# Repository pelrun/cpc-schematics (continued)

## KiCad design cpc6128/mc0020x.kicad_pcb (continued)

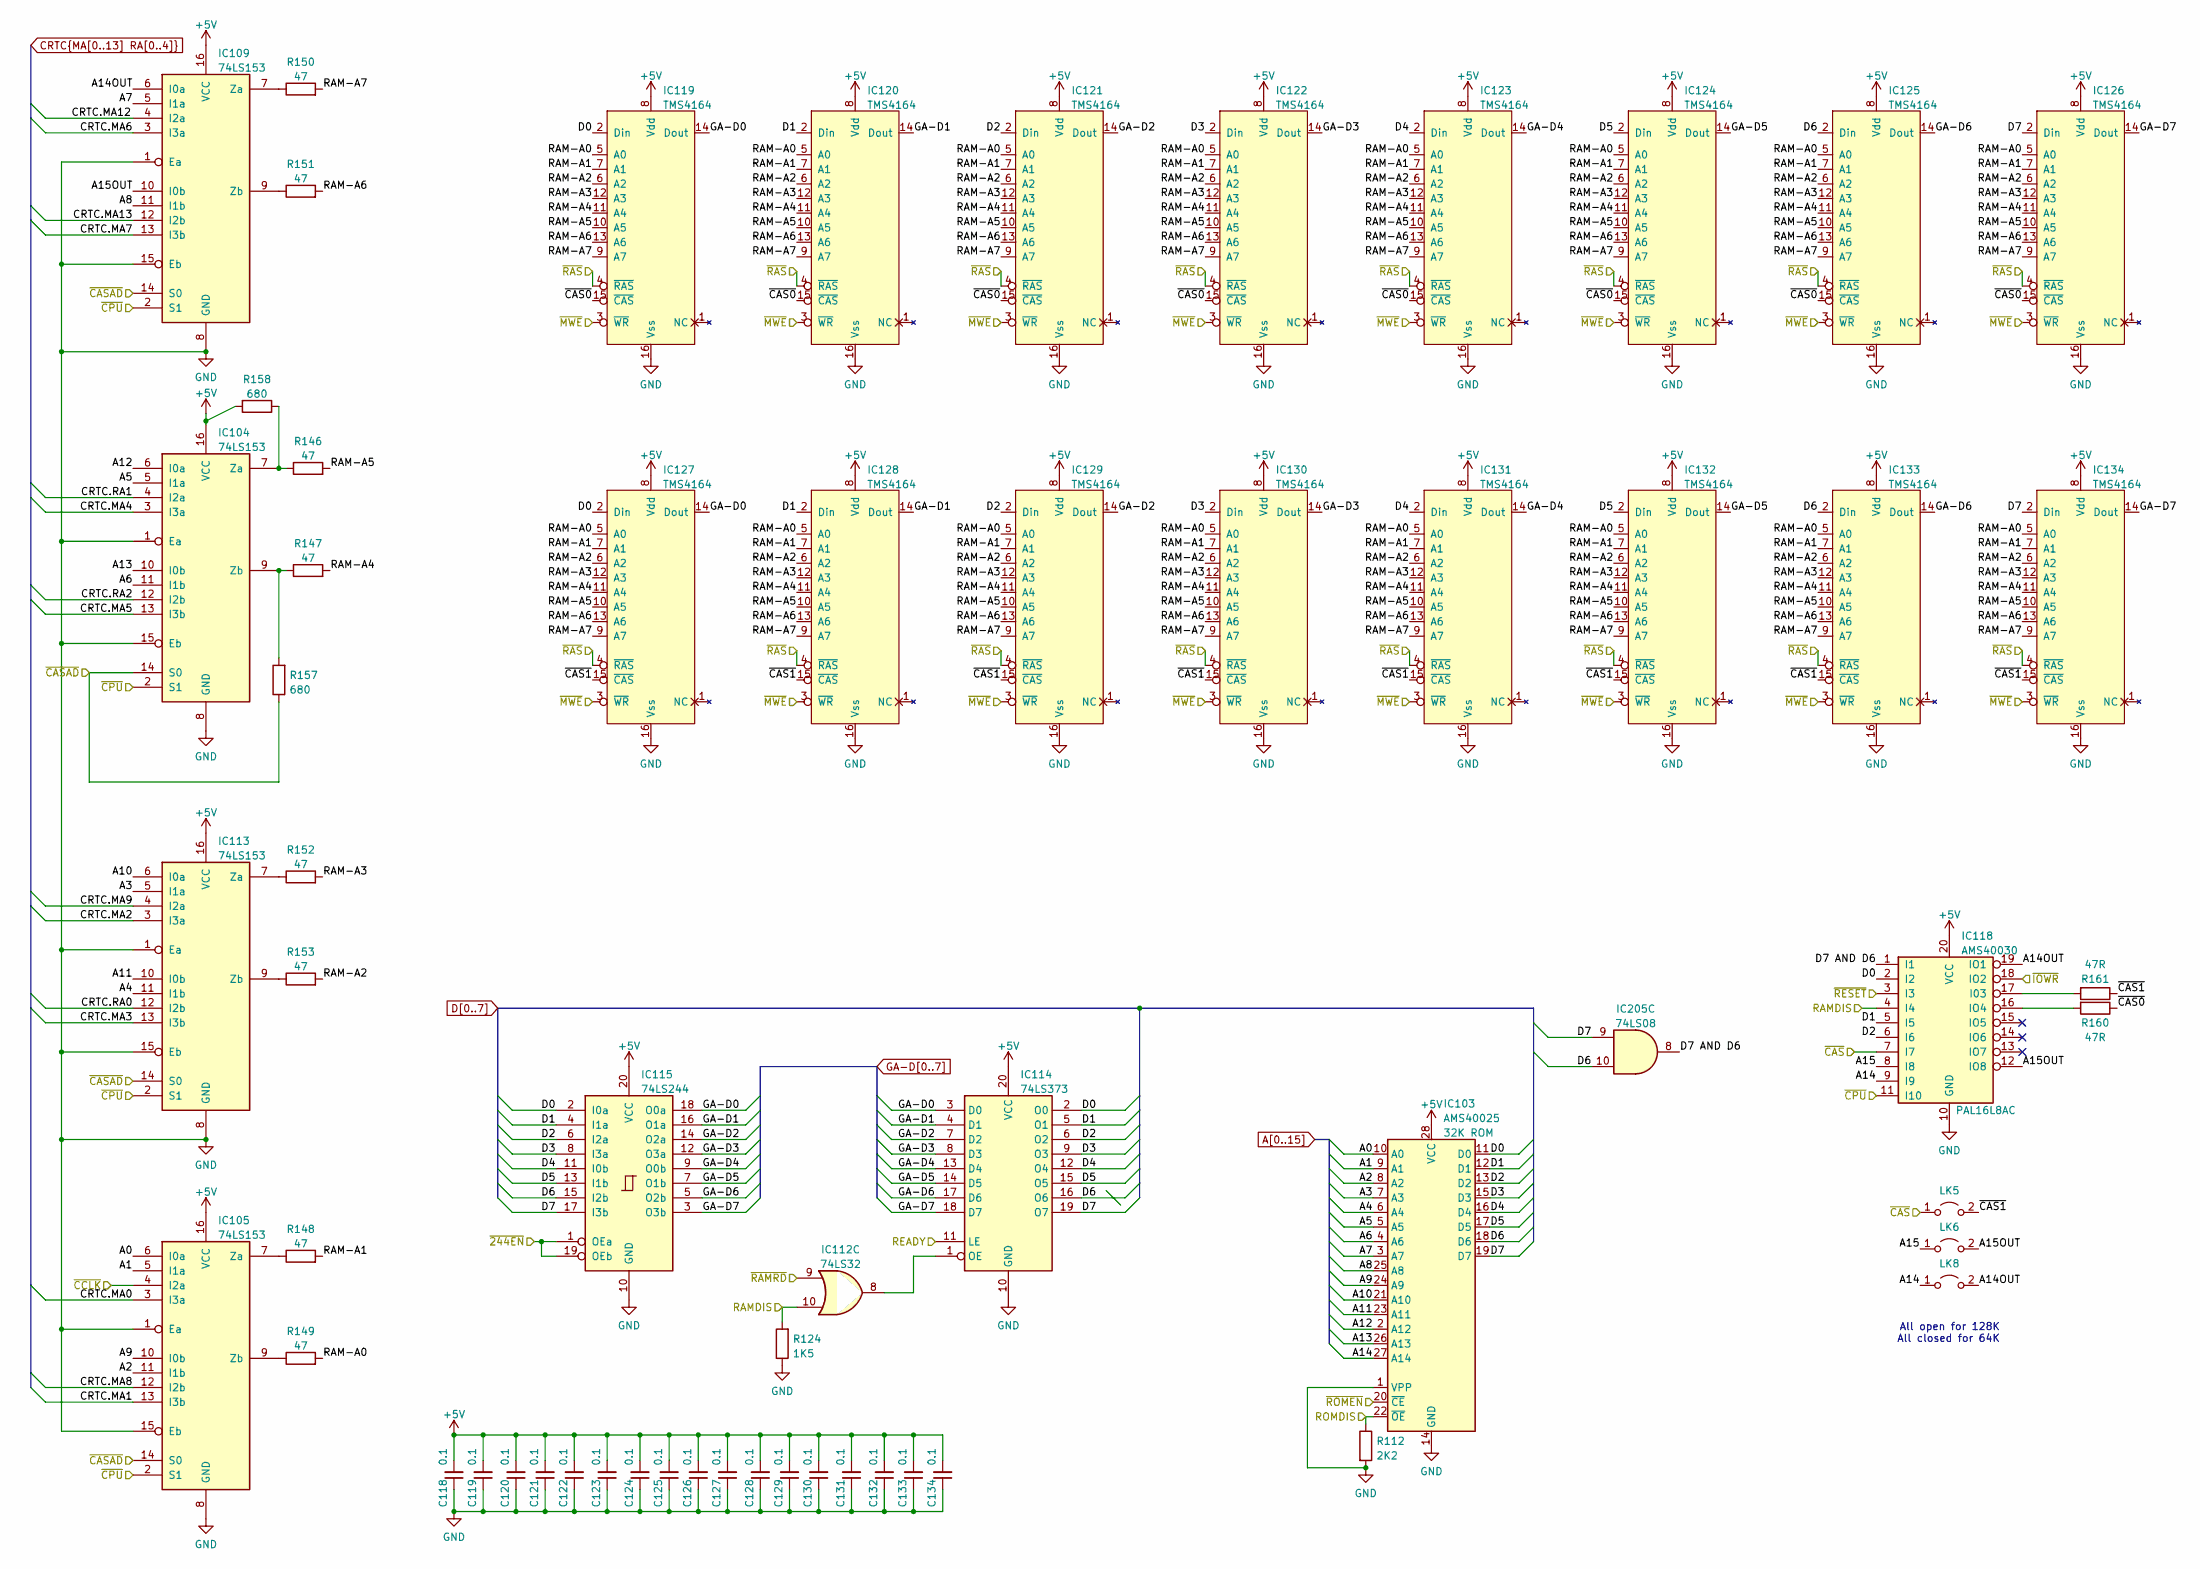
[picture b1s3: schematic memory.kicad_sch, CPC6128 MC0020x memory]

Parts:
C118, C119, C120, C121, C122, C123, C124, C125, C126, C127, C128, C129, C130, C131, C132, C133, C134: 0.1; C_Disc_D4.3mm_W1.9mm_P5.00mm
IC103: AMS40025; DIP-28_W15.24mm
IC104, IC105, IC109, IC113: 74LS153; DIP-16_W7.62mm
IC112: 74LS32; DIP-14_W7.62mm
IC114: 74LS373; DIP-20_W7.62mm
IC115: 74LS244; DIP-20_W7.62mm
IC118: AMS40030; DIP-20_W7.62mm_Socket
IC119, IC120, IC121, IC122, IC123, IC124, IC125, IC126, IC127, IC128, IC129, IC130, IC131, IC132, IC133, IC134: TMS4164; DIP-16_W7.62mm
IC205: 74LS08; DIP-14_W7.62mm
LK5, LK6, LK8: Jumper_2_Open; LINK
R112: 2K2; R_Axial_DIN0207_L6.3mm_D2.5mm_P10.16mm_Horizontal
R124: 1K5; R_Axial_DIN0207_L6.3mm_D2.5mm_P10.16mm_Horizontal
R146, R147, R148, R149, R150, R151, R152, R153: 47; R_Axial_DIN0207_L6.3mm_D2.5mm_P10.16mm_Horizontal
R157, R158: 680; R_Axial_DIN0207_L6.3mm_D2.5mm_P10.16mm_Horizontal
R160, R161: 47R; R_Axial_DIN0207_L6.3mm_D2.5mm_P10.16mm_Horizontal

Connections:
+5V: C118.2, C119.2, C120.2, C121.2, C122.2, C123.2, C124.2, C125.2, C126.2, C127.2, C128.2, C129.2, C130.2, C131.2, C132.2, C133.2, C134.2, IC103.28 (VCC), IC104.16 (VCC), IC105.16 (VCC), IC109.16 (VCC), IC113.16 (VCC), IC114.20 (VCC), IC115.20 (VCC), IC118.20 (VCC), IC119.8 (Vdd), IC120.8 (Vdd), IC121.8 (Vdd), IC122.8 (Vdd), IC123.8 (Vdd), IC124.8 (Vdd), IC125.8 (Vdd), IC126.8 (Vdd), IC127.8 (Vdd), IC128.8 (Vdd), IC129.8 (Vdd), IC130.8 (Vdd), IC131.8 (Vdd), IC132.8 (Vdd), IC133.8 (Vdd), IC134.8 (Vdd), R158.2; also elsewhere on the board
/Memory/A14OUT: IC109.6 (I0a), IC118.19 (IO1), LK8.2 (B)
/Memory/A15OUT: IC109.10 (I0b), IC118.12 (IO8), LK6.2 (B)
/Memory/D7 AND D6: IC118.1 (I1), IC205.8
/Memory/RAM-A0: IC119.5 (A0), IC120.5 (A0), IC121.5 (A0), IC122.5 (A0), IC123.5 (A0), IC124.5 (A0), IC125.5 (A0), IC126.5 (A0), IC127.5 (A0), IC128.5 (A0), IC129.5 (A0), IC130.5 (A0), IC131.5 (A0), IC132.5 (A0), IC133.5 (A0), IC134.5 (A0), R149.2
/Memory/RAM-A1: IC119.7 (A1), IC120.7 (A1), IC121.7 (A1), IC122.7 (A1), IC123.7 (A1), IC124.7 (A1), IC125.7 (A1), IC126.7 (A1), IC127.7 (A1), IC128.7 (A1), IC129.7 (A1), IC130.7 (A1), IC131.7 (A1), IC132.7 (A1), IC133.7 (A1), IC134.7 (A1), R148.2
/Memory/RAM-A2: IC119.6 (A2), IC120.6 (A2), IC121.6 (A2), IC122.6 (A2), IC123.6 (A2), IC124.6 (A2), IC125.6 (A2), IC126.6 (A2), IC127.6 (A2), IC128.6 (A2), IC129.6 (A2), IC130.6 (A2), IC131.6 (A2), IC132.6 (A2), IC133.6 (A2), IC134.6 (A2), R153.2
/Memory/RAM-A3: IC119.12 (A3), IC120.12 (A3), IC121.12 (A3), IC122.12 (A3), IC123.12 (A3), IC124.12 (A3), IC125.12 (A3), IC126.12 (A3), IC127.12 (A3), IC128.12 (A3), IC129.12 (A3), IC130.12 (A3), IC131.12 (A3), IC132.12 (A3), IC133.12 (A3), IC134.12 (A3), R152.2
/Memory/RAM-A4: IC119.11 (A4), IC120.11 (A4), IC121.11 (A4), IC122.11 (A4), IC123.11 (A4), IC124.11 (A4), IC125.11 (A4), IC126.11 (A4), IC127.11 (A4), IC128.11 (A4), IC129.11 (A4), IC130.11 (A4), IC131.11 (A4), IC132.11 (A4), IC133.11 (A4), IC134.11 (A4), R147.2
/Memory/RAM-A5: IC119.10 (A5), IC120.10 (A5), IC121.10 (A5), IC122.10 (A5), IC123.10 (A5), IC124.10 (A5), IC125.10 (A5), IC126.10 (A5), IC127.10 (A5), IC128.10 (A5), IC129.10 (A5), IC130.10 (A5), IC131.10 (A5), IC132.10 (A5), IC133.10 (A5), IC134.10 (A5), R146.2
/Memory/RAM-A6: IC119.13 (A6), IC120.13 (A6), IC121.13 (A6), IC122.13 (A6), IC123.13 (A6), IC124.13 (A6), IC125.13 (A6), IC126.13 (A6), IC127.13 (A6), IC128.13 (A6), IC129.13 (A6), IC130.13 (A6), IC131.13 (A6), IC132.13 (A6), IC133.13 (A6), IC134.13 (A6), R151.2
/Memory/RAM-A7: IC119.9 (A7), IC120.9 (A7), IC121.9 (A7), IC122.9 (A7), IC123.9 (A7), IC124.9 (A7), IC125.9 (A7), IC126.9 (A7), IC127.9 (A7), IC128.9 (A7), IC129.9 (A7), IC130.9 (A7), IC131.9 (A7), IC132.9 (A7), IC133.9 (A7), IC134.9 (A7), R150.2
/Memory/~244EN: IC115.1 (OEa), IC115.19 (OEb); also elsewhere on the board
/Memory/~CAS0: IC119.15 (~CAS), IC120.15 (~CAS), IC121.15 (~CAS), IC122.15 (~CAS), IC123.15 (~CAS), IC124.15 (~CAS), IC125.15 (~CAS), IC126.15 (~CAS), R160.1
/Memory/~CAS1: IC127.15 (~CAS), IC128.15 (~CAS), IC129.15 (~CAS), IC130.15 (~CAS), IC131.15 (~CAS), IC132.15 (~CAS), IC133.15 (~CAS), IC134.15 (~CAS), LK5.2 (B), R161.1
/Memory/~CASAD: IC104.14 (S0), IC105.14 (S0), IC109.14 (S0), IC113.14 (S0), R157.1; also elsewhere on the board
/Memory/~CAS: IC118.7 (I7), LK5.1 (A); also elsewhere on the board
/Memory/~MWE: IC119.3 (~WR), IC120.3 (~WR), IC121.3 (~WR), IC122.3 (~WR), IC123.3 (~WR), IC124.3 (~WR), IC125.3 (~WR), IC126.3 (~WR), IC127.3 (~WR), IC128.3 (~WR), IC129.3 (~WR), IC130.3 (~WR), IC131.3 (~WR), IC132.3 (~WR), IC133.3 (~WR), IC134.3 (~WR); also elsewhere on the board
/Memory/~RAS: IC119.4 (~RAS), IC120.4 (~RAS), IC121.4 (~RAS), IC122.4 (~RAS), IC123.4 (~RAS), IC124.4 (~RAS), IC125.4 (~RAS), IC126.4 (~RAS), IC127.4 (~RAS), IC128.4 (~RAS), IC129.4 (~RAS), IC130.4 (~RAS), IC131.4 (~RAS), IC132.4 (~RAS), IC133.4 (~RAS), IC134.4 (~RAS); also elsewhere on the board
/RAMDIS: IC112.10, IC118.4 (I4), R124.2; also elsewhere on the board
/READY: IC114.11 (LE); also elsewhere on the board
/ROMDIS: IC103.22 (~OE), R112.1; also elsewhere on the board
/~CCLK: IC105.4 (I2a); also elsewhere on the board
/~CPU: IC104.2 (S1), IC105.2 (S1), IC109.2 (S1), IC113.2 (S1), IC118.11 (I10); also elsewhere on the board
/~IOWR: IC118.18 (IO2); also elsewhere on the board
/~RAMRD: IC112.9; also elsewhere on the board
/~RESET: IC118.3 (I3); also elsewhere on the board
/~ROMEN: IC103.20 (~CE); also elsewhere on the board
A0: IC103.10 (A0), IC105.6 (I0a); also elsewhere on the board
A1: IC103.9 (A1), IC105.5 (I1a); also elsewhere on the board
A2: IC103.8 (A2), IC105.11 (I1b); also elsewhere on the board
A3: IC103.7 (A3), IC113.5 (I1a); also elsewhere on the board
A4: IC103.6 (A4), IC113.11 (I1b); also elsewhere on the board
A5: IC103.5 (A5), IC104.5 (I1a); also elsewhere on the board
A6: IC103.4 (A6), IC104.11 (I1b); also elsewhere on the board
A7: IC103.3 (A7), IC109.5 (I1a); also elsewhere on the board
A8: IC103.25 (A8), IC109.11 (I1b); also elsewhere on the board
A9: IC103.24 (A9), IC105.10 (I0b); also elsewhere on the board
A10: IC103.21 (A10), IC113.6 (I0a); also elsewhere on the board
A11: IC103.23 (A11), IC113.10 (I0b); also elsewhere on the board
A12: IC103.2 (A12), IC104.6 (I0a); also elsewhere on the board
A13: IC103.26 (A13), IC104.10 (I0b); also elsewhere on the board
A14: IC103.27 (A14), IC118.9 (I9), LK8.1 (A); also elsewhere on the board
A15: IC118.8 (I8), LK6.1 (A); also elsewhere on the board
CRTC.MA0: IC105.3 (I3a); also elsewhere on the board
CRTC.MA1: IC105.13 (I3b); also elsewhere on the board
CRTC.MA2: IC113.3 (I3a); also elsewhere on the board
CRTC.MA3: IC113.13 (I3b); also elsewhere on the board
CRTC.MA4: IC104.3 (I3a); also elsewhere on the board
CRTC.MA5: IC104.13 (I3b); also elsewhere on the board
CRTC.MA6: IC109.3 (I3a); also elsewhere on the board
CRTC.MA7: IC109.13 (I3b); also elsewhere on the board
CRTC.MA8: IC105.12 (I2b); also elsewhere on the board
CRTC.MA9: IC113.4 (I2a); also elsewhere on the board
CRTC.MA12: IC109.4 (I2a); also elsewhere on the board
CRTC.MA13: IC109.12 (I2b); also elsewhere on the board
CRTC.RA0: IC113.12 (I2b); also elsewhere on the board
CRTC.RA1: IC104.4 (I2a); also elsewhere on the board
CRTC.RA2: IC104.12 (I2b); also elsewhere on the board
D0: IC103.11 (D0), IC114.2 (O0), IC115.2 (I0a), IC118.2 (I2), IC119.2 (Din), IC127.2 (Din); also elsewhere on the board
D1: IC103.12 (D1), IC114.5 (O1), IC115.4 (I1a), IC118.5 (I5), IC120.2 (Din), IC128.2 (Din); also elsewhere on the board
D2: IC103.13 (D2), IC114.6 (O2), IC115.6 (I2a), IC118.6 (I6), IC121.2 (Din), IC129.2 (Din); also elsewhere on the board
D3: IC103.15 (D3), IC114.9 (O3), IC115.8 (I3a), IC122.2 (Din), IC130.2 (Din); also elsewhere on the board
D4: IC103.16 (D4), IC114.12 (O4), IC115.11 (I0b), IC123.2 (Din), IC131.2 (Din); also elsewhere on the board
D5: IC103.17 (D5), IC114.15 (O5), IC115.13 (I1b), IC124.2 (Din), IC132.2 (Din); also elsewhere on the board
D6: IC103.18 (D6), IC114.16 (O6), IC115.15 (I2b), IC125.2 (Din), IC133.2 (Din), IC205.10; also elsewhere on the board
D7: IC103.19 (D7), IC114.19 (O7), IC115.17 (I3b), IC126.2 (Din), IC134.2 (Din), IC205.9; also elsewhere on the board
GA-D0: IC114.3 (D0), IC115.18 (O0a), IC119.14 (Dout), IC127.14 (Dout); also elsewhere on the board
GA-D1: IC114.4 (D1), IC115.16 (O1a), IC120.14 (Dout), IC128.14 (Dout); also elsewhere on the board
GA-D2: IC114.7 (D2), IC115.14 (O2a), IC121.14 (Dout), IC129.14 (Dout); also elsewhere on the board
GA-D3: IC114.8 (D3), IC115.12 (O3a), IC122.14 (Dout), IC130.14 (Dout); also elsewhere on the board
GA-D4: IC114.13 (D4), IC115.9 (O0b), IC123.14 (Dout), IC131.14 (Dout); also elsewhere on the board
GA-D5: IC114.14 (D5), IC115.7 (O1b), IC124.14 (Dout), IC132.14 (Dout); also elsewhere on the board
GA-D6: IC114.17 (D6), IC115.5 (O2b), IC125.14 (Dout), IC133.14 (Dout); also elsewhere on the board
GA-D7: IC114.18 (D7), IC115.3 (O3b), IC126.14 (Dout), IC134.14 (Dout); also elsewhere on the board
GND: C118.1, C119.1, C120.1, C121.1, C122.1, C123.1, C124.1, C125.1, C126.1, C127.1, C128.1, C129.1, C130.1, C131.1, C132.1, C133.1, C134.1, IC103.1 (VPP), IC103.14 (GND), IC104.1 (Ea), IC104.8 (GND), IC104.15 (Eb), IC105.1 (Ea), IC105.8 (GND), IC105.15 (Eb), IC109.1 (Ea), IC109.8 (GND), IC109.15 (Eb), IC113.1 (Ea), IC113.8 (GND), IC113.15 (Eb), IC114.10 (GND), IC115.10 (GND), IC118.10 (GND), IC119.16 (Vss), IC120.16 (Vss), IC121.16 (Vss), IC122.16 (Vss), IC123.16 (Vss), IC124.16 (Vss), IC125.16 (Vss), IC126.16 (Vss), IC127.16 (Vss), IC128.16 (Vss), IC129.16 (Vss), IC130.16 (Vss), IC131.16 (Vss), IC132.16 (Vss), IC133.16 (Vss), IC134.16 (Vss), R112.2, R124.1; also elsewhere on the board
unnamed: IC104.7 (Za), R146.1, R158.1
unnamed: IC104.9 (Zb), R147.1, R157.2
unnamed: IC105.7 (Za), R148.1
unnamed: IC105.9 (Zb), R149.1
unnamed: IC109.7 (Za), R150.1
unnamed: IC109.9 (Zb), R151.1
unnamed: IC113.7 (Za), R152.1
unnamed: IC113.9 (Zb), R153.1
unnamed: IC112.8, IC114.1 (OE)
unnamed: IC118.17 (I03), R161.2
unnamed: IC118.16 (IO4), R160.2

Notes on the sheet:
All open for 128K All closed for 64K

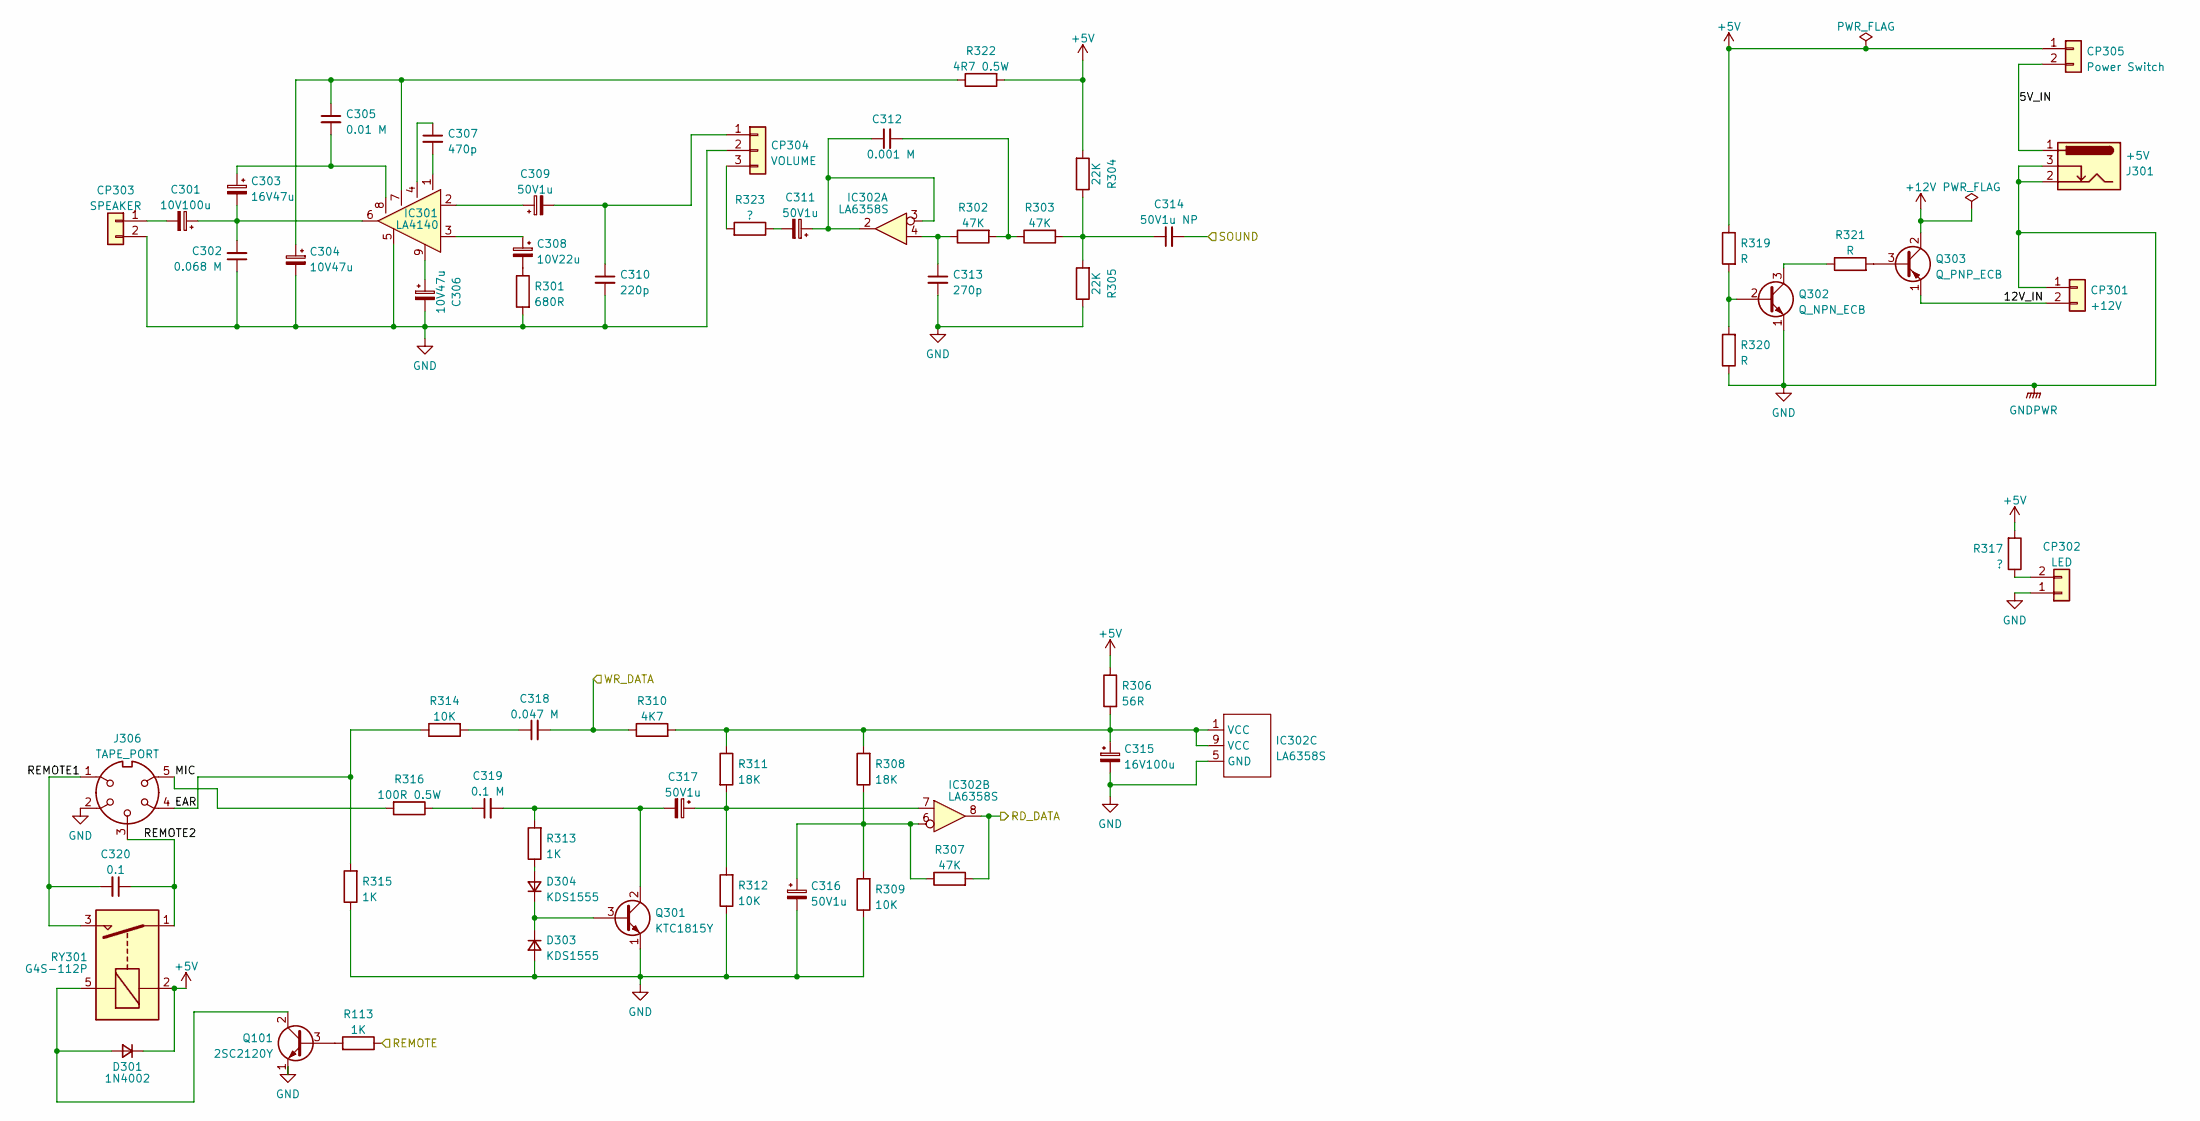
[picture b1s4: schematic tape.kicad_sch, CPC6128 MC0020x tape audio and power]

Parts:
C301: 10V100u; CP_Radial_D4.0mm_P5.00mm
C302: 0.068 M; C_Rect_L7.0mm_W2.0mm_P5.00mm
C303: 16V47u; CP_Radial_D4.0mm_P5.00mm
C304, C306: 10V47u; CP_Radial_D4.0mm_P5.00mm
C305: 0.01 M; C_Rect_L7.0mm_W2.0mm_P5.00mm
C307: 470p; C_Disc_D4.3mm_W1.9mm_P5.00mm
C308: 10V22u; CP_Radial_D4.0mm_P5.00mm
C309, C311, C316, C317: 50V1u; CP_Radial_D4.0mm_P5.00mm
C310: 220p; C_Disc_D4.3mm_W1.9mm_P5.00mm
C312: 0.001 M; C_Rect_L7.0mm_W2.0mm_P5.00mm
C313: 270p; C_Disc_D4.3mm_W1.9mm_P5.00mm
C314: 50V1u NP; C_Radial_D4.0mm_P5.00mm
C315: 16V100u; CP_Radial_D4.0mm_P5.00mm
C318: 0.047 M; C_Rect_L7.0mm_W2.0mm_P5.00mm
C319: 0.1 M; C_Rect_L7.0mm_W2.0mm_P5.00mm
C320: 0.1; C_Disc_D4.3mm_W1.9mm_P5.00mm
CP301: +12V; Molex_KK-254_AE-6410-02A_1x02_P2.54mm_Vertical
CP302: LED; Molex_KK-254_AE-6410-02A_1x02_P2.54mm_Vertical
CP303: SPEAKER; Molex_KK-254_AE-6410-02A_1x02_P2.54mm_Vertical
CP304: VOLUME; Molex_KK-254_AE-6410-03A_1x03_P2.54mm_Vertical
CP305: Power Switch; Molex_KK-254_AE-6410-02A_1x02_P2.54mm_Vertical
D301: 1N4002; D_DO-35_SOD27_P10.16mm_Horizontal
D303, D304: KDS1555; D_DO-35_SOD27_P10.16mm_Horizontal
IC301: LA4140; SIP-9_22.3x3mm_P2.54mm
IC302: LA6358S; SIP-9_22.3x3mm_P2.54mm
J301: +5V; BarrelJack_Wuerth_6941xx301002
J306: TAPE_PORT; TCS4450
Q101: 2SC2120Y; TO-92_Inline_Wide
Q301: KTC1815Y; TO-92_Inline_Wide
Q302: Q_NPN_ECB; TO-92_Inline_Wide
Q303: Q_PNP_ECB; TO-92_Inline_Wide
R113, R313, R315: 1K; R_Axial_DIN0207_L6.3mm_D2.5mm_P10.16mm_Horizontal
R301: 680R; R_Axial_DIN0207_L6.3mm_D2.5mm_P10.16mm_Horizontal
R302, R303, R307: 47K; R_Axial_DIN0207_L6.3mm_D2.5mm_P10.16mm_Horizontal
R304, R305: 22K; R_Axial_DIN0207_L6.3mm_D2.5mm_P10.16mm_Horizontal
R306: 56R; R_Axial_DIN0207_L6.3mm_D2.5mm_P10.16mm_Horizontal
R308, R311: 18K; R_Axial_DIN0207_L6.3mm_D2.5mm_P10.16mm_Horizontal
R309, R312, R314: 10K; R_Axial_DIN0207_L6.3mm_D2.5mm_P10.16mm_Horizontal
R310: 4K7; R_Axial_DIN0207_L6.3mm_D2.5mm_P10.16mm_Horizontal
R316: 100R 0.5W; R_Axial_DIN0207_L6.3mm_D2.5mm_P10.16mm_Horizontal
R317, R323: ?; R_Axial_DIN0207_L6.3mm_D2.5mm_P10.16mm_Horizontal
R319, R320, R321: R; R_Axial_DIN0207_L6.3mm_D2.5mm_P10.16mm_Horizontal
R322: 4R7 0.5W; R_Axial_DIN0207_L6.3mm_D2.5mm_P10.16mm_Horizontal
RY301: G4S-112P; Relay_SPST_SANYOU_SRD_Series_Form_A

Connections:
+5V: CP305.1, D301.1 (K), R304.2, R306.1, R317.2, R319.1, R322.2, RY301.2; also elsewhere on the board
+12V: Q303.2 (C); also elsewhere on the board
/SOUND: C314.2; also elsewhere on the board
/TAPE.RD: IC302.8, R307.2; also elsewhere on the board
/TAPE.WR: C318.2, R310.1; also elsewhere on the board
/Tape/5V_IN: CP305.2, J301.1
/Tape/12V_IN: CP301.2, Q303.1 (E)
/Tape/EAR: J306.4, R314.1, R315.2
/Tape/MIC: J306.5, R316.2
/Tape/REMOTE: R113.1; also elsewhere on the board
/Tape/REMOTE1: C320.2, J306.1, RY301.3
/Tape/REMOTE2: C320.1, J306.3, RY301.1
GND: C302.1, C304.2, C306.2, C310.2, C313.2, C315.2, C316.2, CP301.1, CP302.1, CP303.2, CP304.2, D303.2 (A), IC301.5, IC302.5 (GND), J301.2, J301.3, J306.2, Q101.1 (E), Q301.1 (E), Q302.1 (E), R301.2, R305.1, R309.1, R312.1, R315.1, R320.1; also elsewhere on the board
unnamed: C301.1, C302.2, C303.2, IC301.6
unnamed: C303.1, C305.2, IC301.8
unnamed: C304.1, C305.1, IC301.7, R322.1
unnamed: C306.1, IC301.9
unnamed: C307.1, IC301.4
unnamed: C307.2, IC301.1
unnamed: C308.1, IC301.3
unnamed: C308.2, R301.1
unnamed: C309.1, IC301.2
unnamed: C311.1, C312.1, IC302.2, IC302.3
unnamed: C311.2, R323.1
unnamed: C312.2, R302.2, R303.1
unnamed: C313.1, IC302.4, R302.1
unnamed: C314.1, R303.2, R304.1, R305.2
unnamed: C315.1, IC302.1 (VCC), IC302.9 (VCC), R306.2, R308.2, R310.2, R311.1
unnamed: C316.1, IC302.6, R307.1, R308.1, R309.2
unnamed: C317.1, IC302.7, R311.2, R312.2
unnamed: C318.1, R314.2
unnamed: C319.1, R316.1
unnamed: CP302.2, R317.1
unnamed: C301.2, CP303.1
unnamed: C309.2, C310.1, CP304.1
unnamed: CP304.3, R323.2
unnamed: D301.2 (A), Q101.2 (C), RY301.5
unnamed: D303.1 (K), D304.1 (K), Q301.3 (B)
unnamed: D304.2 (A), R313.1
unnamed: Q101.3 (B), R113.2
unnamed: C317.2, C319.2, Q301.2 (C), R313.2
unnamed: Q302.2 (B), R319.2, R320.2
unnamed: Q302.3 (C), R321.1
unnamed: Q303.3 (B), R321.2

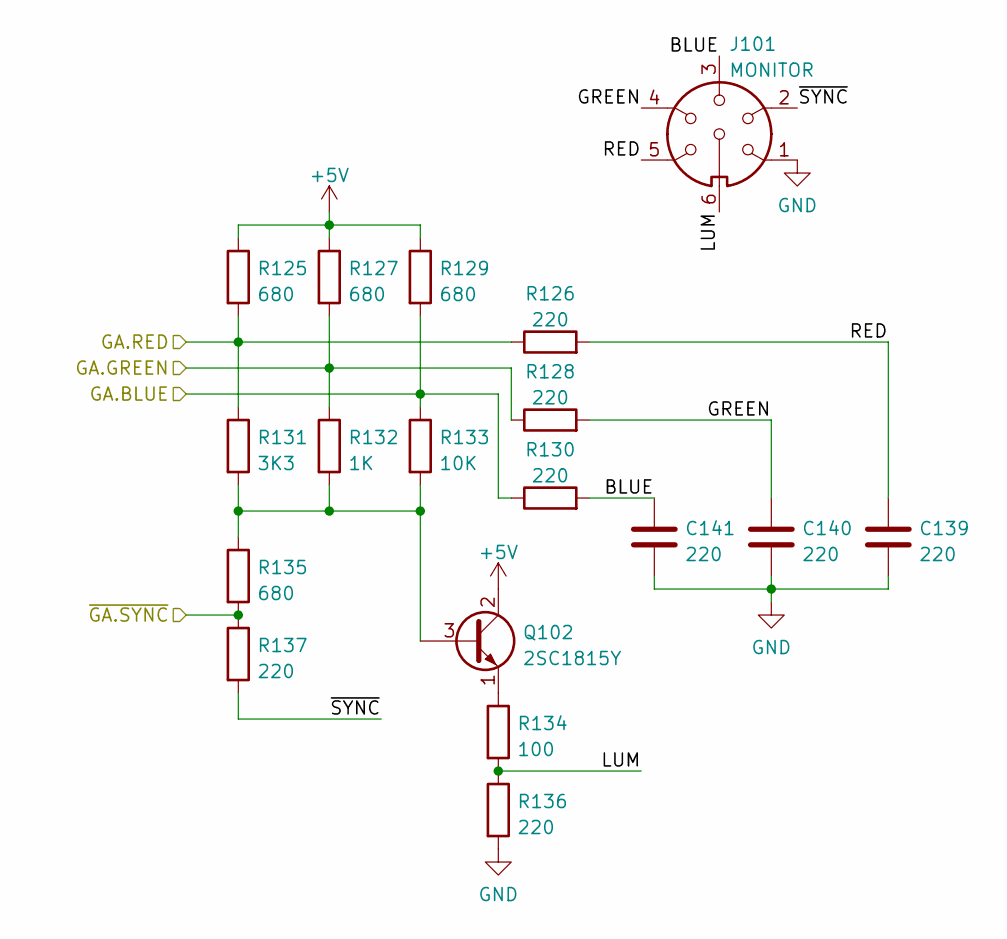
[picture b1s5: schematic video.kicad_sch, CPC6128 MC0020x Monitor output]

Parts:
C139, C140, C141: 220; C_Disc_D4.3mm_W1.9mm_P5.00mm
J101: MONITOR; TCS4460
Q102: 2SC1815Y; TO-92_Inline_Wide
R125, R127, R129, R135: 680; R_Axial_DIN0207_L6.3mm_D2.5mm_P10.16mm_Horizontal
R126, R128, R130, R136, R137: 220; R_Axial_DIN0207_L6.3mm_D2.5mm_P10.16mm_Horizontal
R131: 3K3; R_Axial_DIN0207_L6.3mm_D2.5mm_P10.16mm_Horizontal
R132: 1K; R_Axial_DIN0207_L6.3mm_D2.5mm_P10.16mm_Horizontal
R133: 10K; R_Axial_DIN0207_L6.3mm_D2.5mm_P10.16mm_Horizontal
R134: 100; R_Axial_DIN0207_L6.3mm_D2.5mm_P10.16mm_Horizontal

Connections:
+5V: Q102.2 (C), R125.1, R127.1, R129.1; also elsewhere on the board
/Video/BLUE: C141.1, J101.3, R130.2
/Video/GA.BLUE: R129.2, R130.1, R133.1; also elsewhere on the board
/Video/GA.GREEN: R127.2, R128.1, R132.1; also elsewhere on the board
/Video/GA.RED: R125.2, R126.1, R131.1; also elsewhere on the board
/Video/GREEN: C140.1, J101.4, R128.2
/Video/LUM: J101.6, R134.2, R136.1
/Video/RED: C139.1, J101.5, R126.2
/Video/~GA.SYNC: R135.2, R137.1; also elsewhere on the board
/Video/~SYNC: J101.2, R137.2
GND: C139.2, C140.2, C141.2, J101.1, R136.2; also elsewhere on the board
unnamed: Q102.3 (B), R131.2, R132.2, R133.2, R135.1
unnamed: Q102.1 (E), R134.1

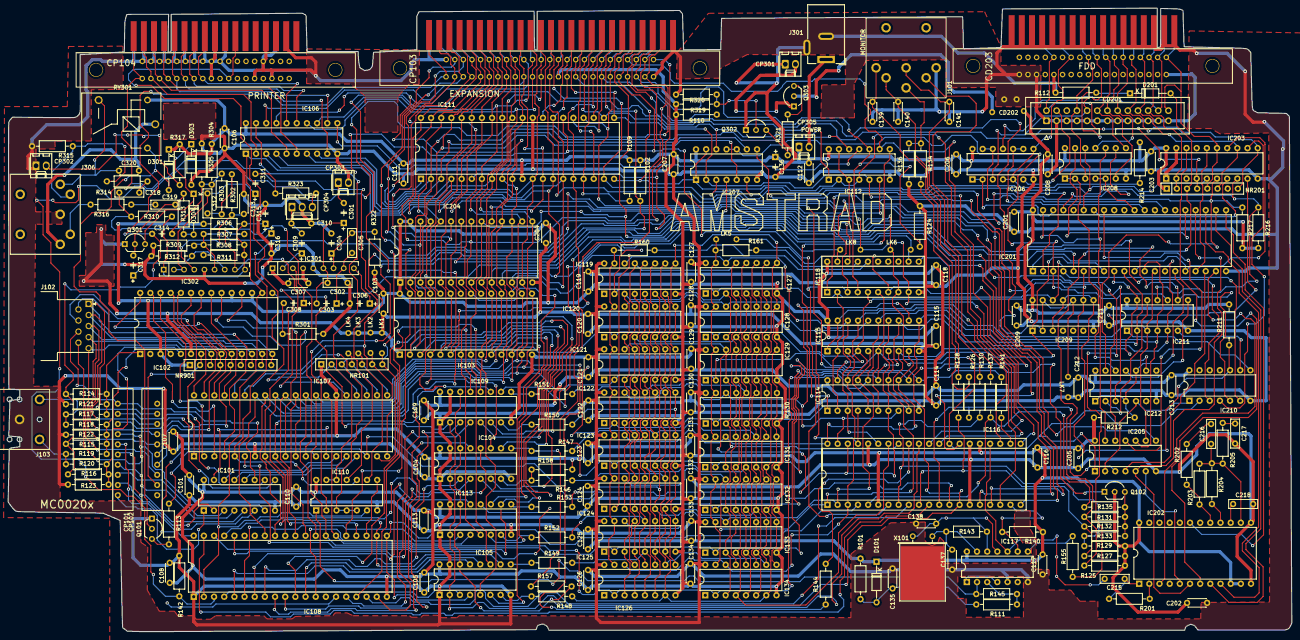
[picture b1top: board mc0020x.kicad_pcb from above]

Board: 2 copper layers, 320.7 x 155.8 mm, 250 parts (1 on the bottom side), 283 nets.

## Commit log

2022-08-20 Initial release
2022-08-20 Update title blocks
2022-08-20 Fix edge connector properties
2022-08-20 Generate pdf outputs
2022-08-21 Fixes from new top pcb image
2022-08-21 Generate iBOM
2022-08-21 Updated with board fixes
2022-08-31 Initial work on nc100
2022-09-01 Minor cleanups
2022-09-05 trace
2025-07-12 Correct C136 (missing) and C314 (wrong footprint) Thanks @orzel!
    Also migrated to KiCad 9.
2025-09-28 Fix swapped audio (thanks @orzel), tweaked some footprints
    PCB layout is unchanged, only affects schematic
